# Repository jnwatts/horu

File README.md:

# What
Replacement logic board and firmware for Micro$oft's Sculpt keyboard

# Why
I really quite like M$'s line of ergonomic keyboards, most recently the Sculpt. Unlike the previous models I've enjoyed, the Sculpt has only a wireless model. While very slick, I'm somewhat concerned about the recent [MouseJack](https://www.mousejack.com/) revelations. From what I've read, my typed data should still be (reasonably) secure, but M$ has yet to announce updated FW for the USB dongle which could allow anyone in range to inject malicious HID packets to my machine. Maybe it's simply impossible to update the FW on the dongle?

# How
To "resolve" this security issue, this project will produce a logic board and firmware to convert the Sculpt to a normal USB keyboard. Currently, I only plan to convert the main keybaord and ignore the floating 10-key device, and I neither have nor care about the associated mouse.

# When
There's no particular time-scale for this project, except that I am already using the Sculpt in it's original state: I'm hoping to develop this board and working firmware before one of my colleages manages to take over my PC with an SDR or something. ;-)

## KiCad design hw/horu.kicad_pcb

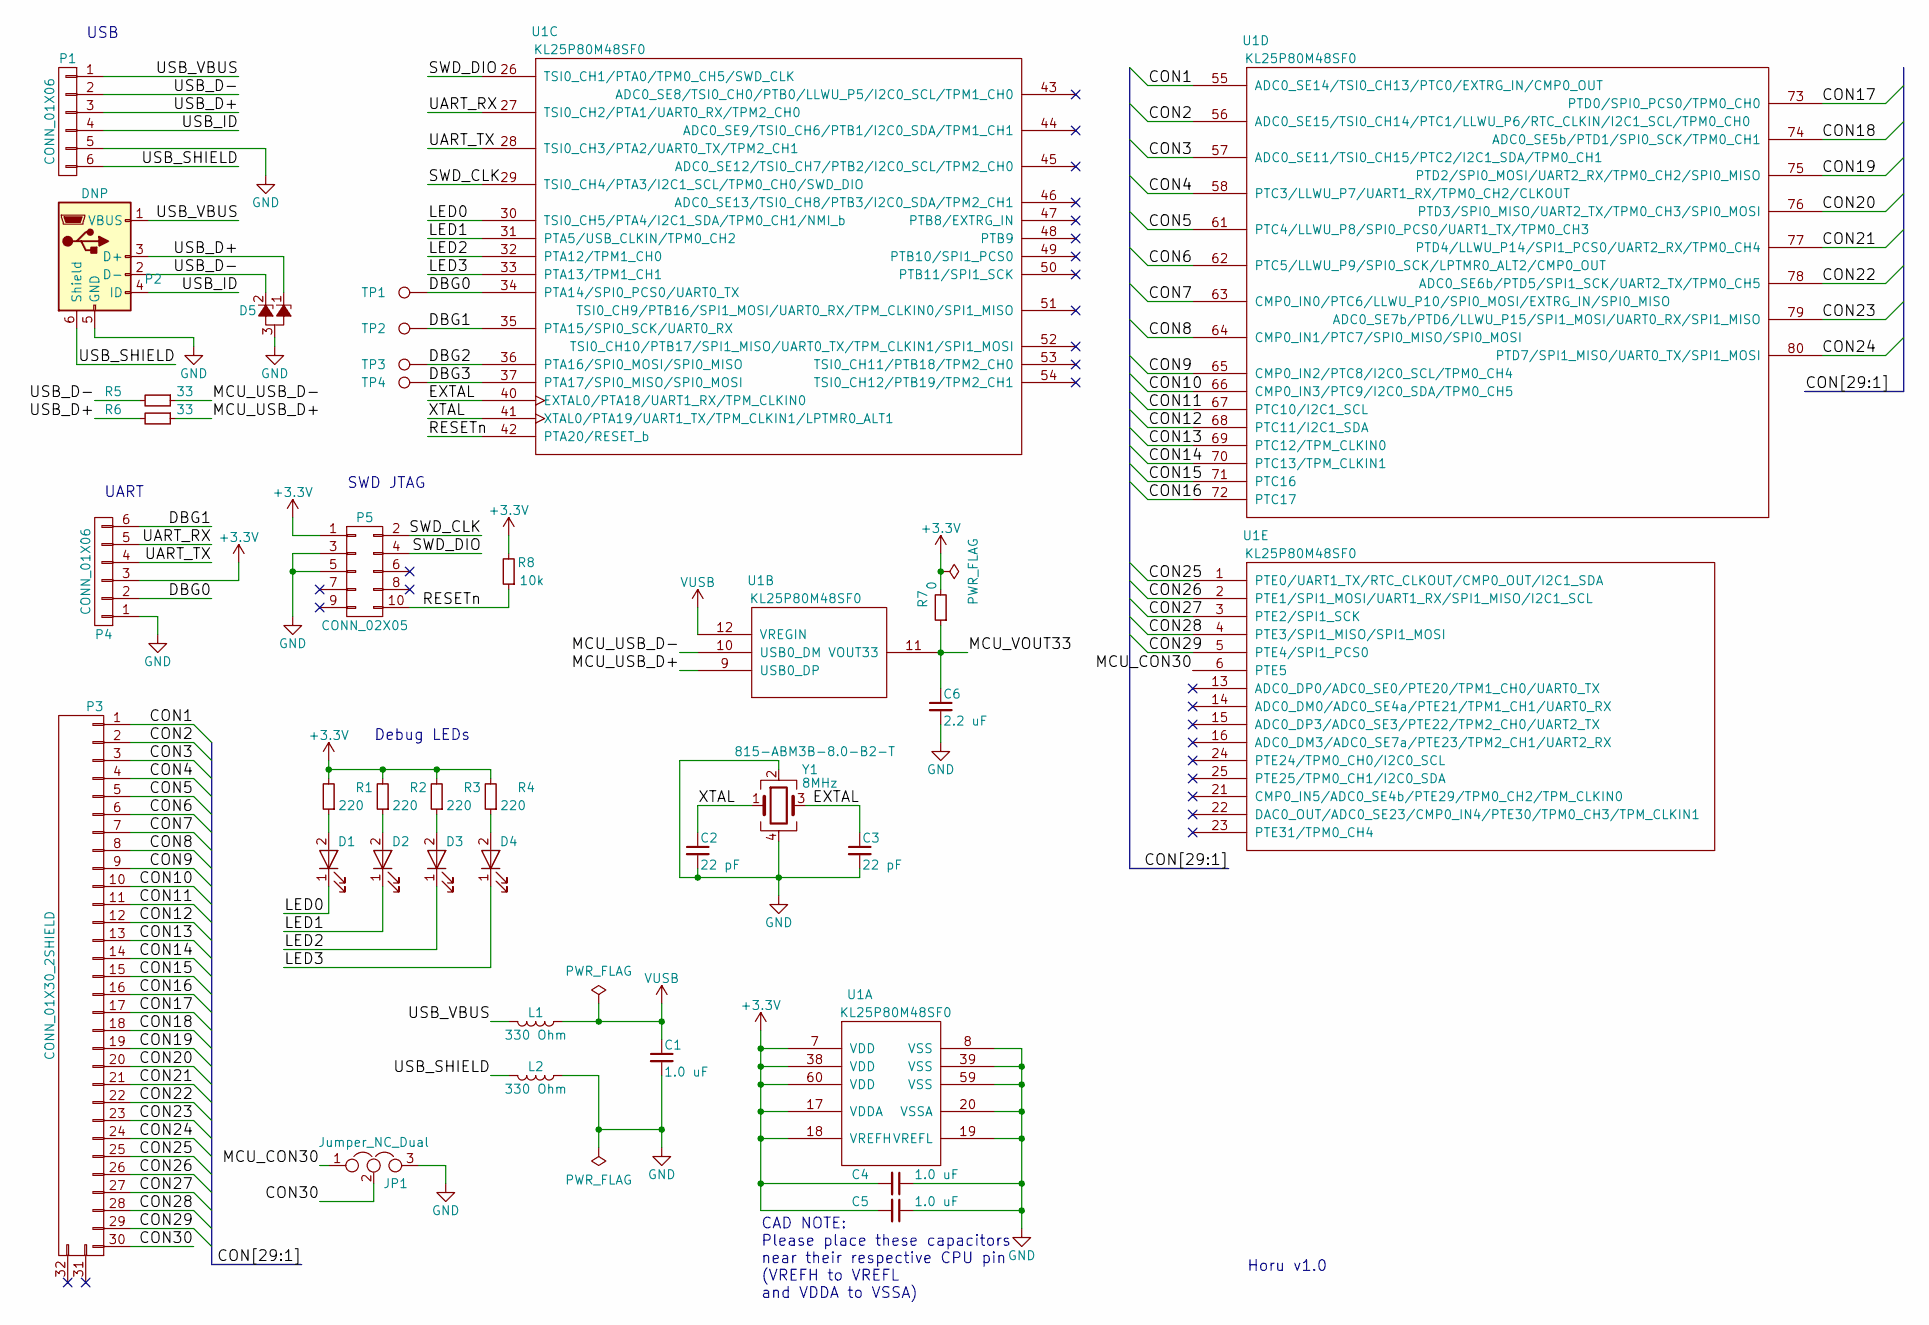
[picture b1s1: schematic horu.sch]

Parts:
C1, C4, C5: 1.0 uF; R_0603_HandSoldering
C2, C3: 22 pF; R_0603_HandSoldering
C6: 2.2 uF; R_0603_HandSoldering
D1, D2, D3, D4: LED_GREEN; LED_0603
D5: D_Zener_x2_ACom_KKA; SOT-23
JP1: Jumper_NC_Dual; GS3
L1, L2: 330 Ohm; R_0603_HandSoldering
P1, P4: CONN_01X06; PINHEAD1-6
P2: DNP; USB_Micro-B
P3: CONN_01X30_2SHIELD; 52271-3079
P5: CONN_02X05; Pin_Header_Straight_2x05_Pitch1.27mm_SMD
R1, R2, R3, R4: 220; R_0603_HandSoldering
R5, R6: 33; R_0603_HandSoldering
R7: 0; R_0402
R8: 10k; R_0603_HandSoldering
TP1, TP2, TP3, TP4: TEST_1P; Measurement_Point_Round-TH_Small
U1: KL25P80M48SF0; LQFP-80_12x12mm_Pitch0.5mm
Y1: 8MHz; Crystal_SMD_Abracon_ABM3B-4pin_5.0x3.2mm

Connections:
+3V3_SDA: C4.2, C5.2, P4.3, P5.1, R1.2, R2.2, R3.2, R4.2, R7.2, R8.2, U1.7 (VDD), U1.17 (VDDA), U1.18 (VREFH), U1.38 (VDD), U1.60 (VDD)
/CON1: P3.1, U1.55 (ADC0_SE14/TSI0_CH13/PTC0/EXTRG_IN/CMP0_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)
/CON2: P3.2, U1.56 (ADC0_SE15/TSI0_CH14/PTC1/LLWU_P6/RTC_CL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)
/CON3: P3.3, U1.57 (ADC0_SE11/TSI0_CH15/PTC2/I2C1_SDA/TPM0_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)
/CON4: P3.4, U1.58 (PTC3/LLWU_P7/UART1_RX/TPM0_CH2/CLKOUT)
/CON5: P3.5, U1.61 (PTC4/LLWU_P8/SPI0_PCS0/UART1_TX/TPM0_CH3)
/CON6: P3.6, U1.62 (PTC5/LLWU_P9/SPI0_SCK/LPTMR0_ALT2/CMP0_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)
/CON7: P3.7, U1.63 (CMP0_IN0/PTC6/LLWU_P10/SPI0_MOSI/EXTRG_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)
/CON8: P3.8, U1.64 (CMP0_IN1/PTC7/SPI0_MISO/SPI0_MOSI)
/CON9: P3.9, U1.65 (CMP0_IN2/PTC8/I2C0_SCL/TPM0_CH4)
/CON10: P3.10, U1.66 (CMP0_IN3/PTC9/I2C0_SDA/TPM0_CH5)
/CON11: P3.11, U1.67 (PTC10/I2C1_SCL)
/CON12: P3.12, U1.68 (PTC11/I2C1_SDA)
/CON13: P3.13, U1.69 (PTC12/TPM_CLKIN0)
/CON14: P3.14, U1.70 (PTC13/TPM_CLKIN1)
/CON15: P3.15, U1.71 (PTC16)
/CON16: P3.16, U1.72 (PTC17)
/CON17: P3.17, U1.73 (PTD0/SPI0_PCS0/TPM0_CH0)
/CON18: P3.18, U1.74 (ADC0_SE5b/PTD1/SPI0_SCK/TPM0_CH1)
/CON19: P3.19, U1.75 (PTD2/SPI0_MOSI/UART2_RX/TPM0_CH2/SPI0_M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)
/CON20: P3.20, U1.76 (PTD3/SPI0_MISO/UART2_TX/TPM0_CH3/SPI0_M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)
/CON21: P3.21, U1.77 (PTD4/LLWU_P14/SPI1_PCS0/UART2_RX/TPM0_C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)
/CON22: P3.22, U1.78 (ADC0_SE6b/PTD5/SPI1_SCK/UART2_TX/TPM0_C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)
/CON23: P3.23, U1.79 (ADC0_SE7b/PTD6/LLWU_P15/SPI1_MOSI/UART0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)
/CON24: P3.24, U1.80 (PTD7/SPI1_MISO/UART0_TX/SPI1_MOSI)
/CON25: P3.25, U1.1 (PTE0/UART1_TX/RTC_CLKOUT/CMP0_OUT/I2C1_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)
/CON26: P3.26, U1.2 (PTE1/SPI1_MOSI/UART1_RX/SPI1_MISO/I2C1_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)
/CON27: P3.27, U1.3 (PTE2/SPI1_SCK)
/CON28: P3.28, U1.4 (PTE3/SPI1_MISO/SPI1_MOSI)
/CON29: P3.29, U1.5 (PTE4/SPI1_PCS0)
/CON30: JP1.2, P3.30
/DBG0: P4.2, TP1.1, U1.34 (PTA14/SPI0_PCS0/UART0_TX)
/DBG1: P4.6, TP2.1, U1.35 (PTA15/SPI0_SCK/UART0_RX)
/DBG2: TP3.1, U1.36 (PTA16/SPI0_MOSI/SPI0_MISO)
/DBG3: TP4.1, U1.37 (PTA17/SPI0_MISO/SPI0_MOSI)
/EXTAL: C3.1, U1.40 (EXTAL0/PTA18/UART1_RX/TPM_CLKIN0), Y1.3
/LED0: D1.1 (K), U1.30 (TSI0_CH5/PTA4/I2C1_SDA/TPM0_CH1/NMI_b)
/LED1: D2.1 (K), U1.31 (PTA5/USB_CLKIN/TPM0_CH2)
/LED2: D3.1 (K), U1.32 (PTA12/TPM1_CH0)
/LED3: D4.1 (K), U1.33 (PTA13/TPM1_CH1)
/MCU_CON30: JP1.1, U1.6 (PTE5)
/MCU_USB_D+: R6.1, U1.9 (USB0_DP)
/MCU_USB_D-: R5.1, U1.10 (USB0_DM)
/MCU_VOUT33: C6.1, R7.1, U1.11 (VOUT33)
/RESETn: P5.10, R8.1, U1.42 (PTA20/RESET_b)
/SWD_CLK: P5.2, U1.29 (TSI0_CH4/PTA3/I2C1_SCL/TPM0_CH0/SWD_DIO)
/SWD_DIO: P5.4, U1.26 (TSI0_CH1/PTA0/TPM0_CH5/SWD_CLK)
/UART_RX: P4.5, U1.27 (TSI0_CH2/PTA1/UART0_RX/TPM2_CH0)
/UART_TX: P4.4, U1.28 (TSI0_CH3/PTA2/UART0_TX/TPM2_CH1)
/USB_D+: D5.1 (K), P1.3, P2.3 (D+), R6.2
/USB_D-: D5.2 (K), P1.2, P2.2 (D-), R5.2
/USB_ID: P1.4, P2.4 (ID)
/USB_SHIELD: L2.2, P1.6, P2.6 (Shield)
/USB_VBUS: L1.2, P1.1, P2.1 (VBUS)
/XTAL: C2.1, U1.41 (XTAL0/PTA19/UART1_TX/TPM_CLKIN1/LPTMR0_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), Y1.1
GND: C1.2, C2.2, C3.2, C4.1, C5.1, C6.2, D5.3 (A), JP1.3, L2.1, P1.5, P2.5 (GND), P4.1, P5.3, P5.5, U1.8 (VSS), U1.19 (VREFL), U1.20 (VSSA), U1.39 (VSS), U1.59 (VSS), Y1.2, Y1.4
unnamed: D1.2 (A), R1.1
unnamed: D2.2 (A), R2.1
unnamed: D3.2 (A), R3.1
unnamed: D4.2 (A), R4.1
VUSB: C1.1, L1.1, U1.12 (VREGIN)

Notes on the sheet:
CAD NOTE: Please place these capacitors near their respective CPU pin (VREFH to VREFL and VDDA to VSSA)
USB
UART
SWD JTAG
Debug LEDs
Horu v1.0

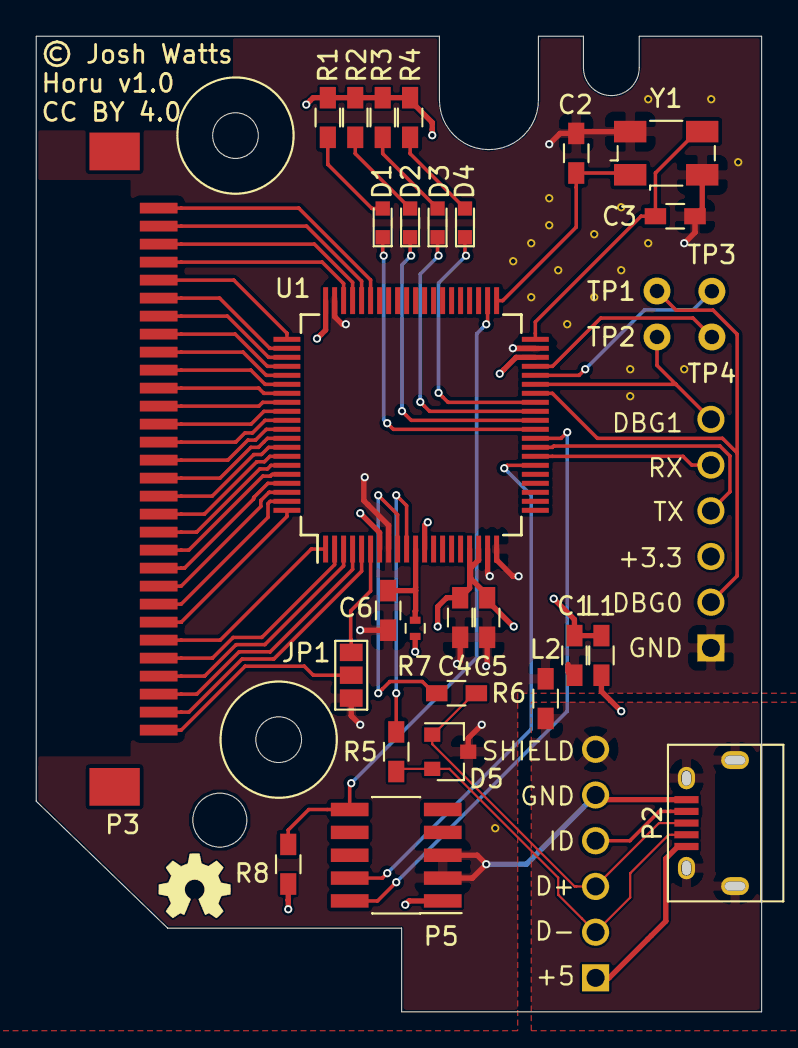
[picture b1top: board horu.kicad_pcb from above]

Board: 4 copper layers, 40.3 x 54.2 mm, 33 parts (0 on the bottom side), 61 nets.

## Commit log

2016-08-16 Add photos of original board
2017-02-05 Initial commit of HW
    * OpenSDA region complete
    * Cleaner KL25 symbol (not yet placed)
2017-02-06 Schematic complete except for decoupling
2017-02-09 Define some footprints
2017-02-09 Drop opensda circuit
    This makes room in BOM for fancy USB switch letting either USB-C port be connected to PC, while other can connect (in future) to keypad
2017-02-09 Add submodule repos
2017-02-09 Add footprint for molex FPC
2017-02-10 Add some more footprints
2017-02-26 Add caliper measurements
2017-02-27 Update to v0.1 release
    * Fall back to simple mUSB-B (connector + pigtail supported)
    * First pass at layout
    * Added missing pull-up to RESETn
2017-02-27 Release v0.1
2017-02-28 Changed to copper pour for each layer
2017-02-28 Release v0.2
2017-03-19 Update schematic and prepare for release
    * Update rev to v1.0
    * Update USB_OTG symbol
    * Add missing USB ESD diodes
    * Fill in manf# for all parts
    * Export BOM using kicost
    * Fill ground on bottom layer
2017-03-19 Update design
    * Fix JP101 -> JP1
    * Update USB_OTG -> DNP
2017-03-19 Rev v1.0
    * Remove not-so-useful release folder
    * Update schematic and layout pdfs
2017-04-18 Add tmk_core
2017-04-18 Add ChibiOS
2017-05-21 STASH: Got it to compile... still need to customize
2017-05-21 horu: Update pin mux
2017-05-21 horu: Update LED & DBG lines
2017-05-21 horu: Update copyright
2017-05-21 horu: Rename board
2017-05-21 horu: Add gitignore
2017-06-27 Makefile: Add shortcuts for launching openocd & gdb
2020-01-25 Update to KiCad 5.1.5 & replace EOL capacitors

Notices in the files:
hw/horu.kicad_pcb:
© Josh Watts
CC BY 4.0
